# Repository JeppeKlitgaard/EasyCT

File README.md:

# EasyCT

## Terminology

- Burden Resistor: Also known as *sampling resistor*

## Supported Inputs

EasyCT supports most current-mode current transformers
(that is, current transformers without a built-in burden resistor).
These will have their outputs listed as currents (typically $\textrm{mA}$ or $\textrm{A}$),
__not__ voltages ($\textrm{mV, V}$) 

Additionally the PCB footprint has support for the following transformers:
- Three Terminal Jacks (known as TRS, AUX, XLR)
  - [YHDC-SCT013-000](https://www.poweruc.pl/collections/split-core-current-transformers2/products/split-core-current-transformer-sct013-rated-input-5a-100a)
- 2-Wire
  - PZCT10020 (generally PZCT-XXXXX, etc)
  - DLXQ26-XXXX
- ZMCT-style
  - ZMCT103C
  - ZMCT118F

## Supported Configurations

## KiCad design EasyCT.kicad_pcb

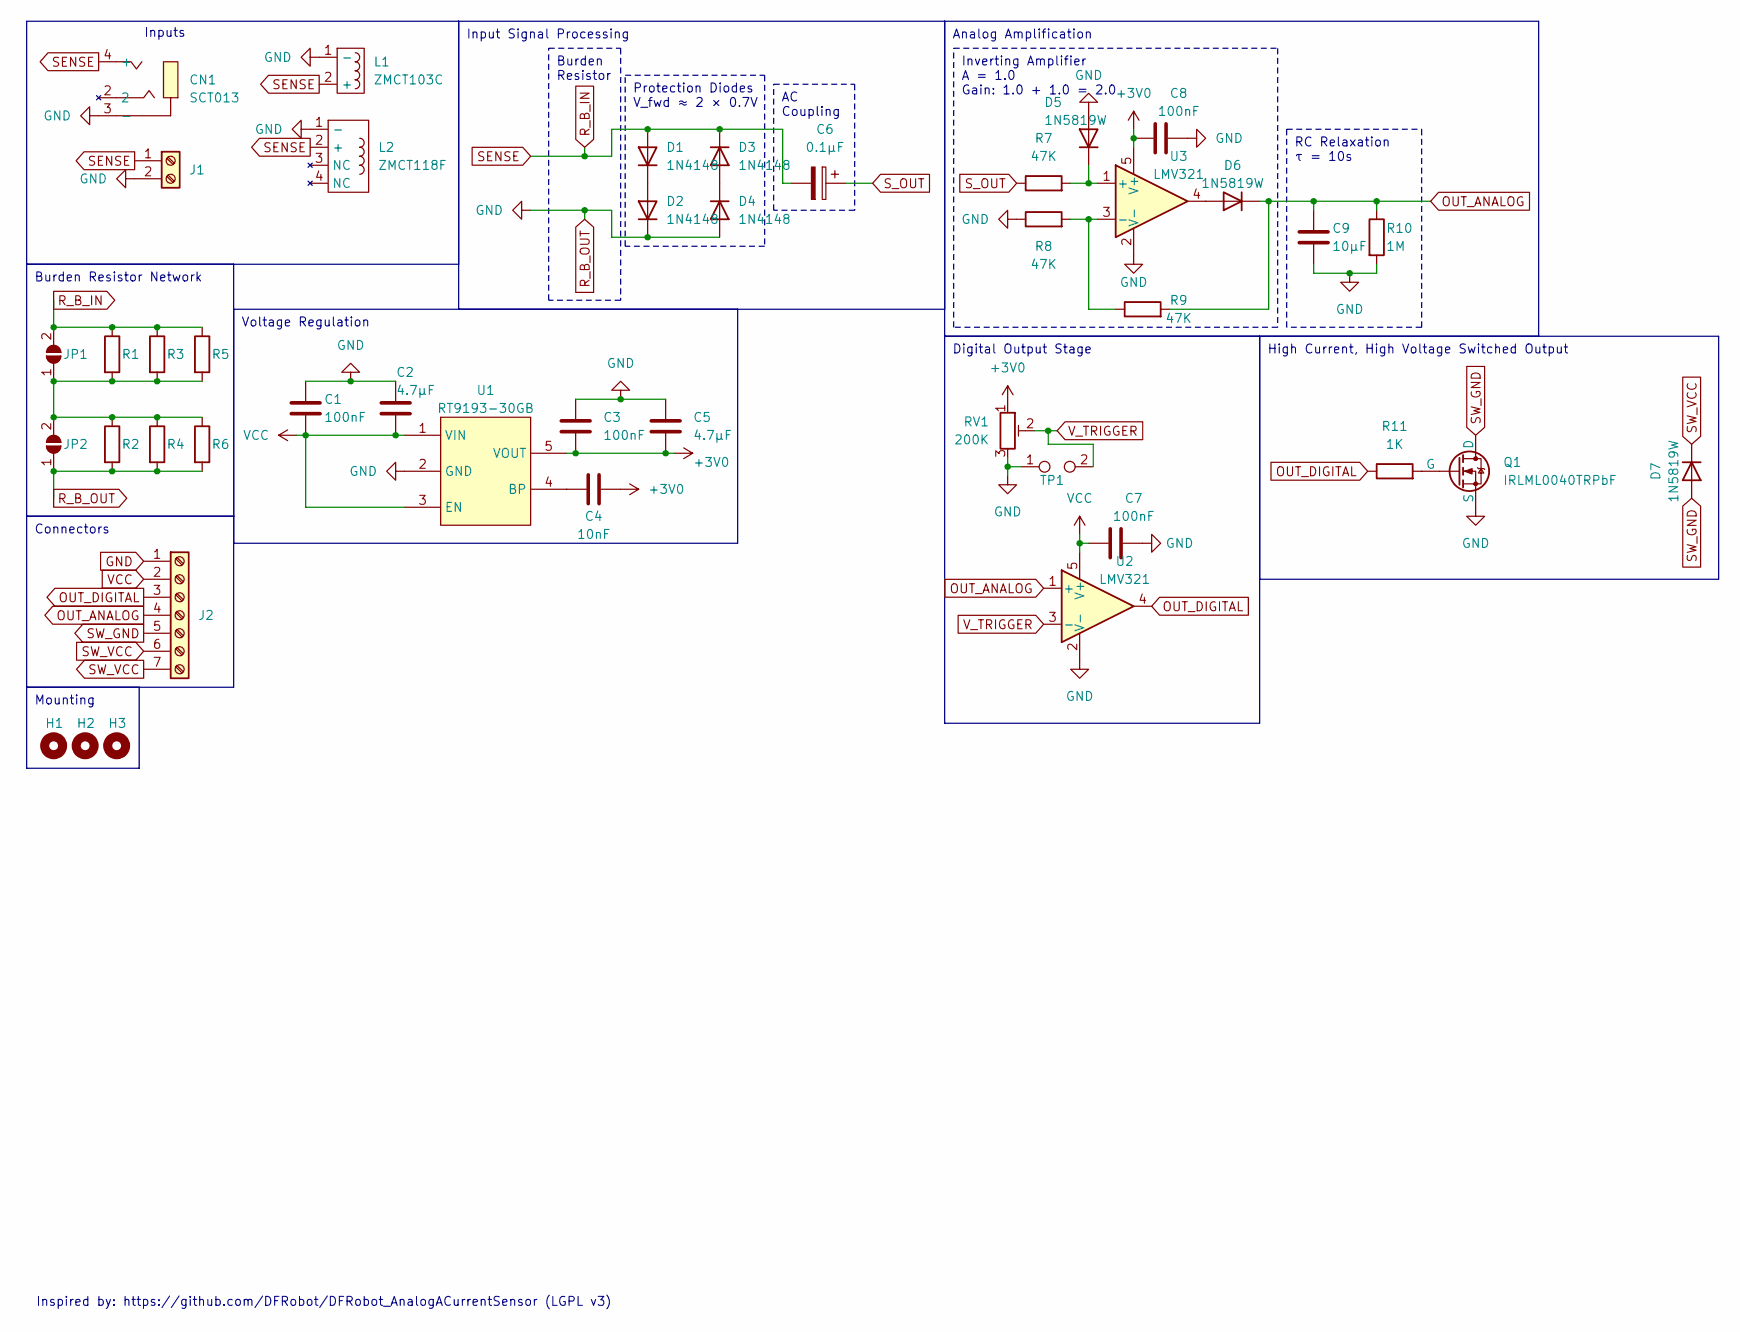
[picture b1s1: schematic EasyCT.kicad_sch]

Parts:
C1, C3, C7, C8: 100nF; C_0805_2012Metric
C2, C5: 4.7μF; C_0805_2012Metric
C4: 10nF; C_0805_2012Metric
C6: 0.1μF; C_0805_2012Metric
C9: 10μF; C_0805_2012Metric
CN1: SCT013; AUDIO-TH_HOOYA_PJ-320
D1, D2, D3, D4: 1N4148; D_SOD-123
D5, D6, D7: 1N5819W; D_SOD-323
H1, H2, H3: MountingHole; MountingHole_3.2mm_M3
J1: Screw_Terminal_01x02; CONN-TH_XY308-2.54-2P
J2: Screw_Terminal_01x07; CONN-TH_XY308-2.54-7P
JP1, JP2: SolderJumper_2_Open; SolderJumper-2_P1.3mm_Open_TrianglePad1.0x1.5mm
L1: ZMCT103C; Current_Transformer_CT_ZMCT103C
L2: ZMCT118F; XFMR-TH_ZMCT118F
Q1: IRLML0040TRPbF; SOT-23
R1, R2, R3, R4, R5, R6: R; R_Axial_DIN0207_L6.3mm_D2.5mm_P7.62mm_Horizontal
R7, R8, R9: 47K; R_0805_2012Metric
R10: 1M; R_0805_2012Metric
R11: 1K; R_0805_2012Metric
RV1: 200K; Potentiometer_Bourns_3296W_Vertical
TP1: TestPoint_2Pole; TestPoint_2Pads_Pitch5.08mm_Drill1.3mm
U1: RT9193-30GB; SOT-23-5_L3.0-W1.7-P0.95-LS2.8-BR; LCSC Part C50004
U2, U3: LMV321; SOT-23-5

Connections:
+3V0: C3.2, C4.1, C5.2, C8.1, RV1.1, U1.5 (VOUT), U3.5 (V+)
GND: C1.1, C2.1, C3.1, C5.1, C7.2, C8.2, C9.2, CN1.3 (-), D2.1 (K), D4.2 (A), D5.2 (A), J1.2, J2.1, JP2.1 (A), L1.1 (-), L2.1 (-), Q1.3 (S), R2.2, R4.2, R6.2, R8.1, R10.2, RV1.3, TP1.1, U1.2 (GND), U2.2 (V-), U3.2 (V-)
unnamed: D1.1 (K), D2.2 (A)
unnamed: D3.2 (A), D4.1 (K)
unnamed: D5.1 (K), R7.2, U3.1 (+)
unnamed: D6.2 (A), U3.4
unnamed: JP1.1 (A), JP2.2 (B), R1.2, R2.1, R3.2, R4.1, R5.2, R6.1
unnamed: Q1.2 (G), R11.2
unnamed: C4.2, U1.4 (BP)
unnamed: R8.2, R9.1, U3.3 (-)
OUT_ANALOG: C9.1, D6.1 (K), J2.4, R9.2, R10.1, U2.1 (+)
OUT_DIGITAL: J2.3, R11.1, U2.4
R_B_IN: C6.2, CN1.4 (+), D1.2 (A), D3.1 (K), J1.1, JP1.2 (B), L1.2 (+), L2.2 (+), R1.1, R3.1, R5.1
SW_GND: D7.2 (A), J2.5, Q1.1 (D)
SW_VCC: D7.1 (K), J2.6, J2.7
S_OUT: C6.1, R7.1
VCC: C1.2, C2.2, C7.1, J2.2, U1.1 (VIN), U1.3 (EN), U2.5 (V+)
V_TRIGGER: RV1.2, TP1.2, U2.3 (-)

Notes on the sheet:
Protection Diodes V_fwd ≈ 2 × 0.7V
RC Relaxation τ = 10s
Input Signal Processing
AC Coupling
Mounting
High Current, High Voltage Switched Output
Inverting Amplifier A = 1.0 Gain: 1.0 + 1.0 = 2.0
Burden Resistor Network
Analog Amplification
Burden Resistor
Digital Output Stage
Voltage Regulation
Connectors
Inputs
Inspired by: https://github.com/DFRobot/DFRobot_AnalogACurrentSensor (LGPL v3)

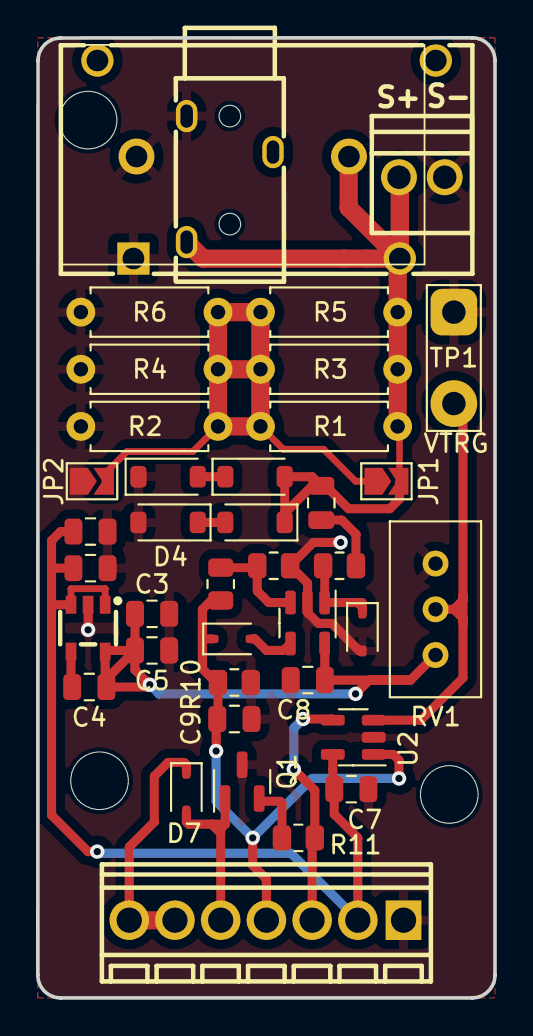
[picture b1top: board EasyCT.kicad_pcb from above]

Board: 2 copper layers, 25.4 x 53.3 mm, 43 parts (0 on the bottom side), 18 nets.

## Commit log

2023-08-31 feat: finish v1, send to JLCPCB
